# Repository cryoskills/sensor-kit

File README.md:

# Cryoskills 2024 - Sensor Kit
This repository contains the design notes, schematics, EDA files (KiCad), fabrication documents and firmware for the CryoSkills sensor kit.

## Folder Structure

- `design_notes/`: design notes and documentation.

- `cad/`: electronic and mechanical design files, separated into:
    - `kicad/` schematic and PCB layout files
    - `freecad/` mechanical design files

- `fabrication/`: resources required to purchase, fabricate and assemble a sensor kit (bill of materials, Gerber files, drawings, etc.).

- `firmware/`: complete and skeleton firmware for the sensor kit.

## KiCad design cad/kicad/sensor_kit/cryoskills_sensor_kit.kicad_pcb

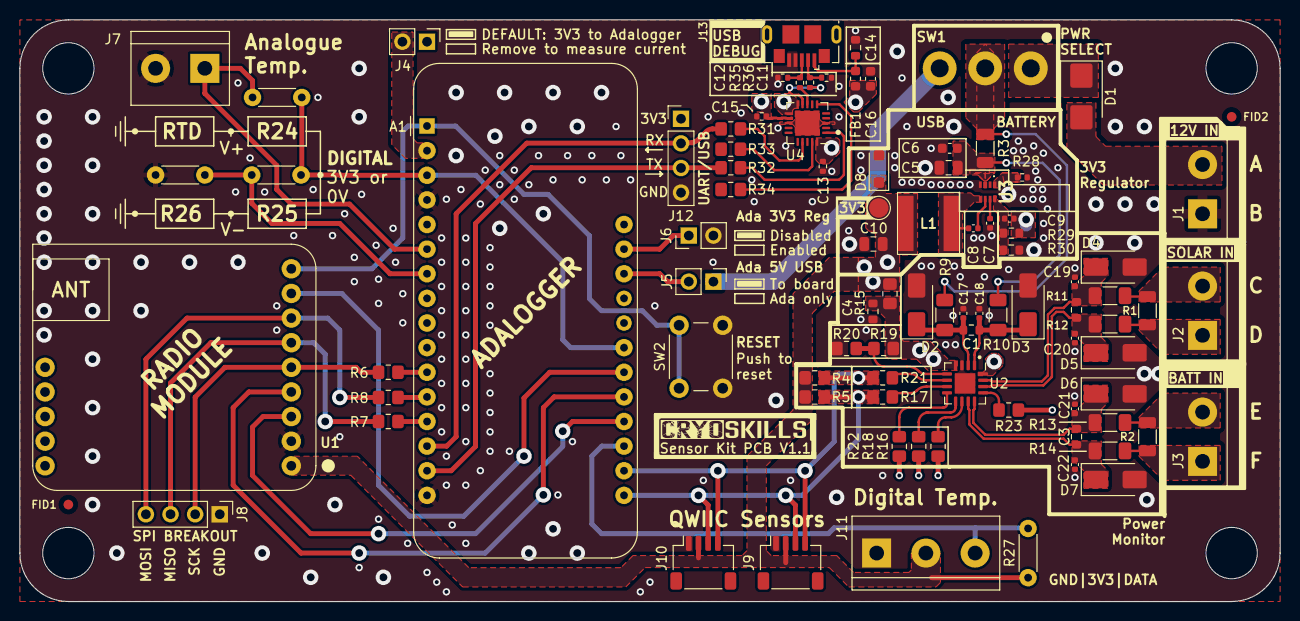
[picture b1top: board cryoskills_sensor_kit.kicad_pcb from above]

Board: 2 copper layers, 130.0 x 60.0 mm, 95 parts (0 on the bottom side), 58 nets.

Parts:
A1: Adafruit_Feather_M0_Adalogger; Adafruit_Feather
C1, C2, C3, C4: 0.1 uF; R_0603_1608Metric
C5: 10uF; C_0805_2012Metric
C6: 100nF; C_0603_1608Metric
C7: 33nF; C_0402_1005Metric
C8, C17, C18, C19, C20, C21, C22: 100nF; C_0402_1005Metric
C9: 47pF; C_0402_1005Metric
C10: 22uF; C_0805_2012Metric
C11, C12: 47pF; R_0402_1005Metric
C13, C15: 100nF; R_0402_1005Metric
C14: 10nF; R_0603_1608Metric
C16: 4.7uF; C_0603_1608Metric
D1: D; D_SMB
D2, D3, D4, D5, D6, D7: SMAJ16A-13-F; D_SMA
D8: NZH3V6B,115; D_SOD-123F
FB1: FerriteBead; L_0603_1608Metric
FID1, FID2: Fiducial; Fiducial_1mm_Mask2mm
H1, H2, H3, H4: MountingHole; MountingHole_5.3mm_M5
J1: PWR_In; TerminalBlock_Multicomp_5.08_2way_MP012059
J2: PWR_SENSE_Panel; TerminalBlock_Multicomp_5.08_2way_MP012059
J3: PWR_SENSE_Battery; TerminalBlock_Multicomp_5.08_2way_MP012059
J4: Adalogger_3V3; PinHeader_1x02_P2.54mm_Vertical
J5: Adalogger_VBUS; PinHeader_1x02_P2.54mm_Vertical
J6: Adalogger_RegulatorEN; PinHeader_1x02_P2.54mm_Vertical
J7: PT1000_RTD_WHEAT; TerminalBlock_Multicomp_5.08_2way_MP012059
J8: SPI_BREAKOUT; PinHeader_1x04_P2.54mm_Vertical
J9: QWIIC_I2C_1; JST_SH_SM04B-SRSS-TB_1x04-1MP_P1.00mm_Horizontal
J10: QWIIC_I2C_2; JST_SH_SM04B-SRSS-TB_1x04-1MP_P1.00mm_Horizontal
J11: DS18B20; TerminalBlock_Multicomp_5.08_3way_MP012060
J12: SERIAL_BREAKOUT; PinHeader_1x04_P2.54mm_Vertical
J13: USB_B; USB_Micro-B_GCT_USB3076-30-A
L1: 2.7uH; 1255AY-2R7N#
R1, R2, R3: 0.1 Ohm; R_1206_3216Metric
R4, R5: 4.7k; R_0805_2012Metric_Pad1.20x1.40mm_HandSolder
R6, R7, R8, R15, R17, R20, R21, R31, R32, R33, R34: 0R; R_0805_2012Metric_Pad1.20x1.40mm_HandSolder
R9, R10, R11, R12, R13, R14: 10 Ohm; R_1206_3216Metric_Pad1.30x1.75mm_HandSolder
R16, R18, R22, R23: 10k; R_0805_2012Metric_Pad1.20x1.40mm_HandSolder
R19: DNF; R_0805_2012Metric_Pad1.20x1.40mm_HandSolder
R24, R25: 3k3; R_Axial_DIN0204_L3.6mm_D1.6mm_P5.08mm_Horizontal
R26: 1k; R_Axial_DIN0204_L3.6mm_D1.6mm_P5.08mm_Horizontal
R27: 4.7k; R_Axial_DIN0204_L3.6mm_D1.6mm_P5.08mm_Horizontal
R28: 15k; R_0402_1005Metric
R29: 30.9k; R_0603_1608Metric
R30: 10k; R_0603_1608Metric
R35, R36: 27R; R_0402_1005Metric
SW1: SPDT Switch; RSPRO_7347334_SWSlide_SPDT
SW2: SW_Push; SW_PUSH_6mm
TP1: 3V3; TestPoint_Pad_D2.0mm
U1: RFM96W
U2: INA3221; Texas_RGV_S-PVQFN-N16_EP2.1x2.1mm
U3: TPS62932DRLR
U4: FT231XQ; QFN-20-1EP_4x4mm_P0.5mm_EP2.5x2.5mm

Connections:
/ADC_REF+: A1.3 (AREF), A1.23 (D11), R24.1, R25.1
/ADC_RTDm: A1.7 (A2), R25.2, R26.1
/ADC_RTDp: A1.6 (A1), J7.1, R24.2
/DS18B20_DATA: A1.19 (D5), J11.3, R27.2
/Isense_Battery_A: J3.2, R2.2, R13.1
/Isense_Battery_B: J3.1, R2.1, R14.1
/Isense_Panel_A: J2.2, R1.2, R11.1
/Isense_Panel_B: J2.1, R1.1, R12.1
/Isense_VCC_A: R3.2, R9.1, SW1.2 (B)
/Isense_VCC_B: C5.1, C6.1, R3.1, R10.1, U3.3 (VIN)
/MISO: J8.3, R7.1, U1.6 (MISO)
/MOSI: J8.4, R8.1, U1.7 (MOSI)
/Power Monitor/INA3221_I2CAddress: R19.2, R20.1, U2.5 (A0)
/Power Monitor/INA3221_IN1+: C3.2, C21.2, D6.1 (K), R13.2, U2.12 (IN+1)
/Power Monitor/INA3221_IN1-: C3.1, C22.2, D7.1 (K), R14.2, U2.11 (IN-1)
/Power Monitor/INA3221_IN2+: C2.2, C19.2, D4.1 (K), R11.2, U2.15 (IN+2)
/Power Monitor/INA3221_IN2-: C2.1, C20.2, D5.1 (K), R12.2, U2.14 (IN-2)
/Power Monitor/INA3221_IN3+: C1.2, C17.2, D2.1 (K), R9.2, U2.2 (IN+3)
/Power Monitor/INA3221_IN3-: C1.1, C18.2, D3.1 (K), R10.2, U2.1 (IN-3)
/Power Monitor/VCC_INA3221: C4.2, R15.2, R16.1, R18.1, R19.1, R22.1, R23.1, U2.4 (VS), U2.16 (VPU)
/RADIO_CS: A1.22 (D10), U1.8 (CS)
/RADIO_EN: A1.20 (D6), U1.3 (EN)
/RADIO_IRQ: A1.21 (D9), U1.4 (G0)
/SCK: J8.2, R6.1, U1.5 (SCK)
/SCL: A1.18 (SCL/D21), J9.4, J10.4, R4.2, R21.2
/SDA: A1.17 (SDA/D20), J9.3, J10.3, R5.2, R17.2
/UART_RXuC: A1.14 (RX/D0), J12.2, R31.2
/UART_TXuC: A1.15 (TX/D1), J12.3, R32.2
/VBUS_Adalogger: A1.26 (USB), J5.2
/VCC_3V3: C9.1, C10.1, D8.1 (K), J4.1, J9.2, J10.2, J11.2, J12.1, L1.2, R4.1, R5.1, R15.1, R27.1, R29.1, TP1.1, U1.1 (VIN)
/VCC_3V3_Adalogger: A1.2 (3V3), J4.2
/V_BAT: D1.2 (A), J1.2
/V_BUS: J5.1, SW1.3 (C)
/~RESET: A1.1 (~RESET), SW2.1, U1.9 (~RST)
GND: A1.4 (GND), A1.16 (GND), C4.1, C5.2, C6.2, C7.2, C10.2, C11.1, C12.1, C13.1, C14.2, C15.1, C16.2, C17.1, C18.1, C19.1, C20.1, C21.1, C22.1, D2.2 (A), D3.2 (A), D4.2 (A), D5.2 (A), D6.2 (A), D7.2 (A), D8.2 (A), J1.1, J6.2, J7.2, J8.1, J9.1, J10.1, J11.1, J12.4, J13.4 (GND), J13.5 (Shield), R20.2, R26.2, R28.2, R30.2, SW2.2, U1.2 (GND), U2.3 (GND), U2.17 (EP), U3.4 (GND), U4.3 (GND), U4.13 (GND), U4.21 (GND)
unnamed: A1.27 (EN), J6.1
unnamed: A1.13 (MISO/D22), R7.2
unnamed: A1.12 (MOSI/D23), R8.2
unnamed: A1.11 (SCK/D24), R6.2
unnamed: D1.1 (K), SW1.1 (A)
unnamed: C12.2, J13.3 (D+), R35.1
unnamed: C11.2, J13.2 (D-), R36.1
unnamed: C14.1, FB1.1, J13.1 (VBUS)
unnamed: R21.1, U2.6 (SCL)
unnamed: R17.1, U2.7 (SDA)
unnamed: C8.1, U3.6 (BST)
unnamed: C9.2, R29.2, R30.1, U3.8 (FB)
unnamed: R28.1, U3.1 (RT)
unnamed: C7.1, U3.7 (SS)
unnamed: C8.2, L1.1, U3.5 (SW)
unnamed: C13.2, U4.10 (3V3OUT), U4.11 (~RESET), U4.20 (VCCIO)
unnamed: R32.1, U4.1 (RXD)
unnamed: R31.1, U4.17 (TXD)
unnamed: R36.2, U4.9 (USBDM)
unnamed: R35.2, U4.8 (USBDP)
unnamed: C15.2, C16.1, FB1.2, U4.12 (VCC)
unnamed: R34.1, U4.6 (~CTS)
unnamed: R33.1, U4.19 (~RTS)

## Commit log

2024-01-11 adds design notes for power supply and initial outline of power schematic
2024-01-11 moves sensors to new board and adds discussion around ADS1120 based analog temp sensor to design notes.
2024-01-25 adds further sensors to board layout
2024-01-25 adds python gitignore
2024-01-25 adds design notes for analog temp sensor
2024-01-25 adds initial schematic
2024-01-29 add skeleton code for prototype, using DS18B20 and BME280 temp sensors
2024-02-02 updates sensorkit PCB with revised pinout and wheatstone bridge circuit
2024-02-16 makes small PCB modifications
2024-02-20 revises sensor board to remove current source and reduce footprint
2024-03-07 fixes MISO/MOSI on RFM96, swaps Dp/Dm on USB and makes pads for THT resistors bigger
2024-03-08 corrects MISO/MIMO silkscreen labels
2024-03-21 separate header files for different functions
2024-03-26 pushes latest version of schematic
2024-03-26 pushes correct version of schematic, not the no-power version
2024-03-31 updates production files from sensor kit materials
2024-04-18 adds relevant libraries as submodules
2024-04-18 adds skeleton to get analogue and digital temperature with SD card debugging
2024-04-18 adds radio and SD card data logging
2024-04-25 updates datalogger firmware (with Arduino IDE and PlatformIO files)
2024-04-25 adds MIT License to datalogger-2024.ino/main.cpp and resets sensor ID
